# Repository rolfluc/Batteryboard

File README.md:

# Batteryboard
Castillated module to use on other devices.

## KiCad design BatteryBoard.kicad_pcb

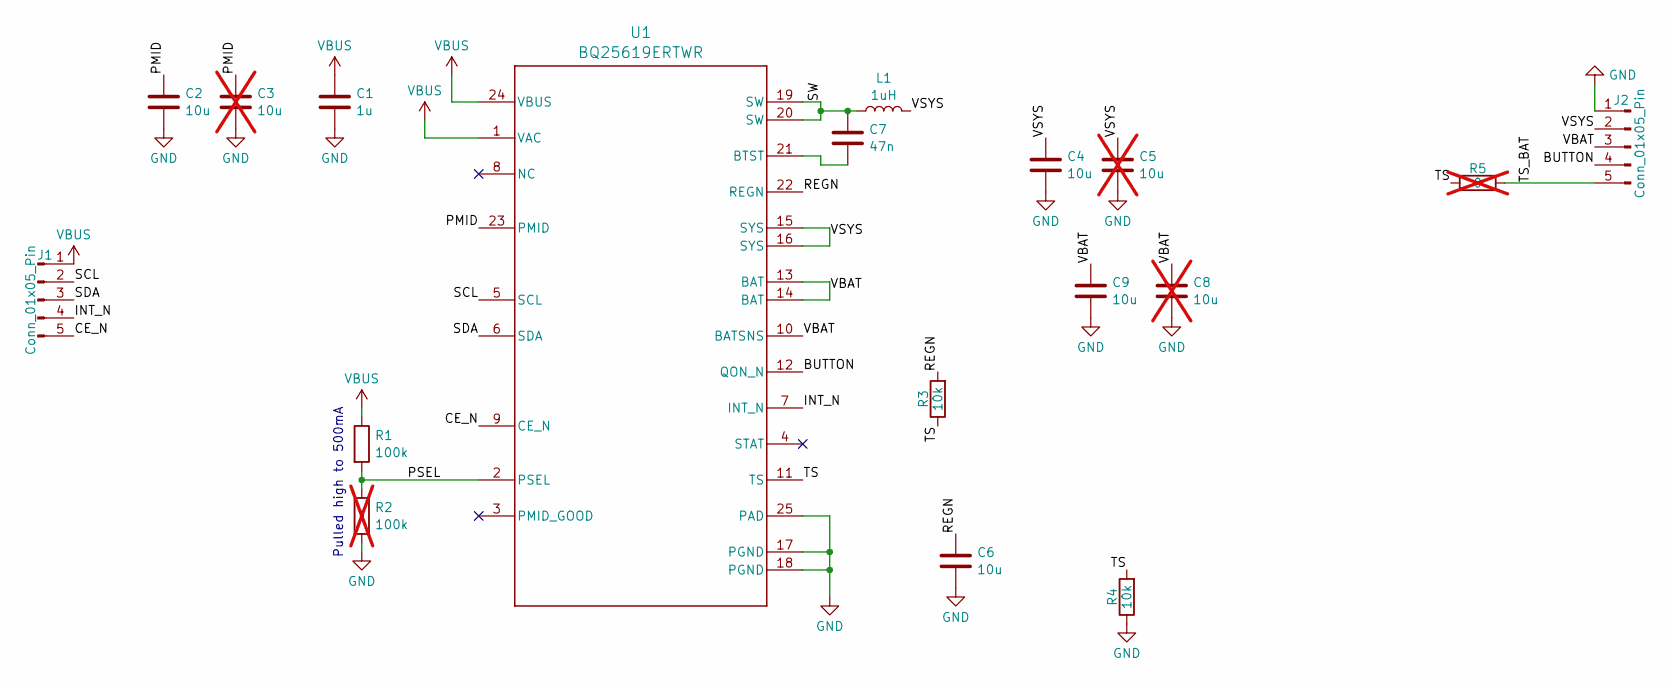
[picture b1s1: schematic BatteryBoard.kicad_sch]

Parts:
C1: 1u; C_0402_1005Metric; MPN CL05A105KA5NQNC
C2, C4, C6, C9: 10u; C_0402_1005Metric; MPN CL05A106MP8NUB8
C3, C5, C8: 10u; C_0402_1005Metric; MPN CL05A106MP8NUB8; not fitted
C7: 47n; C_0402_1005Metric; MPN CL05B473KB5VPNC
J1, J2: Conn_01x05_Pin; 5_Castellated
L1: 1uH; L_1008_2520Metric; MPN LQM2HPN1R0MGHL
R1: 100k; R_0402_1005Metric; MPN RC0402FR-07100KL
R2: 100k; R_0402_1005Metric; MPN RC0402FR-07100KL; not fitted
R3, R4: 10k; R_0402_1005Metric; MPN RC0402JR-0710KL
R5: 0; R_0402_1005Metric; not fitted
U1: BQ25619ERTWR; RTW0024P; MPN BQ25619ERTWR

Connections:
/BUTTON: J2.4, U1.12 (QON_N)
/CE_N: J1.5, U1.9 (CE_N)
/INT_N: J1.4, U1.7 (INT_N)
/PMID: C2.1, C3.1, U1.23 (PMID)
/PSEL: R1.2, R2.1, U1.2 (PSEL)
/REGN: C6.1, R3.2, U1.22 (REGN)
/SCL: J1.2, U1.5 (SCL)
/SDA: J1.3, U1.6 (SDA)
/SW: C7.1, L1.1, U1.19 (SW), U1.20 (SW)
/TS: R3.1, R4.2, R5.1, U1.11 (TS)
/TS_BAT: J2.5, R5.2
/VBAT: C8.1, C9.1, J2.3, U1.10 (BATSNS), U1.13 (BAT), U1.14 (BAT)
/VSYS: C4.1, C5.1, J2.2, L1.2, U1.15 (SYS), U1.16 (SYS)
GND: C1.2, C2.2, C3.2, C4.2, C5.2, C6.2, C8.2, C9.2, J2.1, R2.2, R4.1, U1.17 (PGND), U1.18 (PGND), U1.25 (PAD)
unnamed: C7.2, U1.21 (BTST)
VBUS: C1.1, J1.1, R1.1, U1.1 (VAC), U1.24 (VBUS)

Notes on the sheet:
Pulled high to 500mA

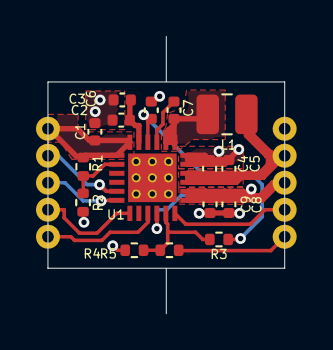
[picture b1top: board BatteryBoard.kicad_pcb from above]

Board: 4 copper layers, 13.1 x 15.4 mm, 18 parts (0 on the bottom side), 16 nets.

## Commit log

2026-01-21 Basic Schematic Output, basic placement
2026-01-21 Board Outline and placement Completed
2026-01-21 Minor Update for Routing
2026-01-21 Out to Review
2026-01-21 Minor Change
2026-01-26 BOM Continuation
2026-01-26 BOM Update
2026-01-27 Missed Pull up for TS, updated Bulk caps to 10u, and added more DNP
2026-01-27 Castelated edges upodate, relayout for TS Resistor
2026-01-27 Teardropped Vias
2026-01-27 Gerbers and Output Files
2026-01-27 Updating BOM for LCSC Part #s
2026-01-27 Thickened Traces a little
2026-01-27 Cleanup, and ordered boards
